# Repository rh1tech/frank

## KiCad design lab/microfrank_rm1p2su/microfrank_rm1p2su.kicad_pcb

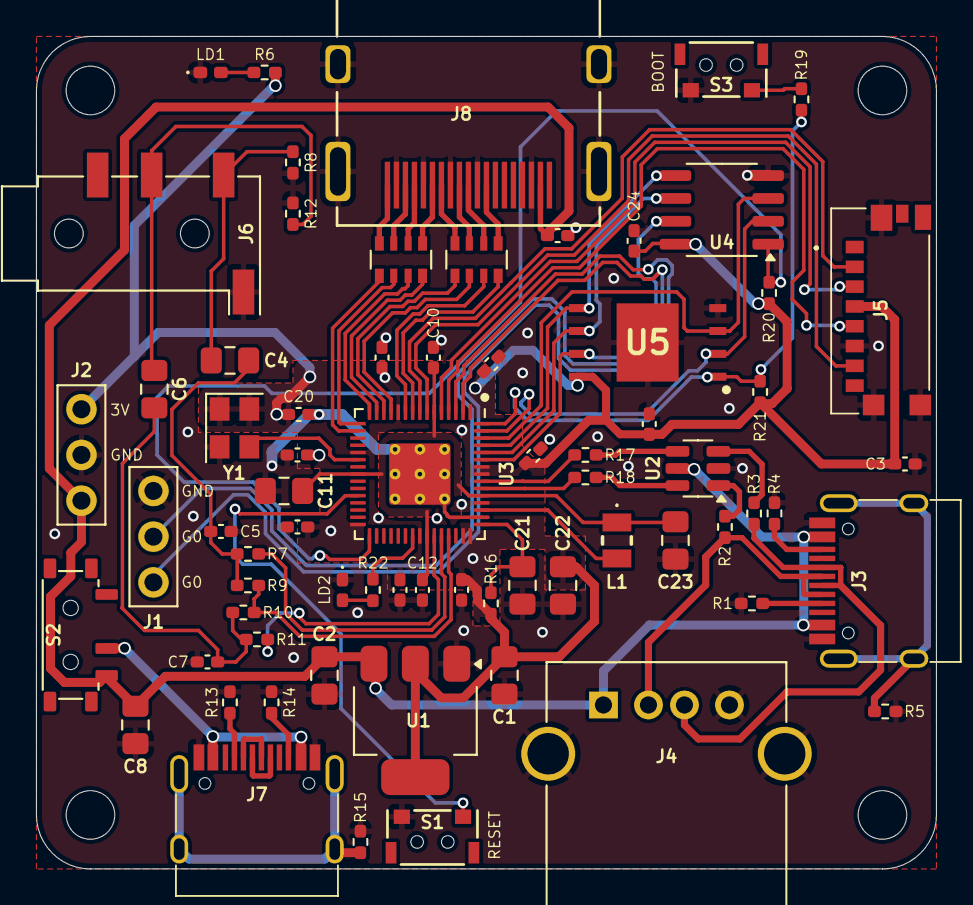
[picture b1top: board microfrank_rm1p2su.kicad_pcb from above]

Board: 2 copper layers, 50.0 x 46.2 mm, 73 parts (0 on the bottom side), 65 nets.

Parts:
C1, C2, C4, C6, C8: 10u; Capacitor (0805)
C3, C9, C10, C12, C13, C14, C15, C16, C17, C18, C19, C20, C24, C25: 100n; Capacitor (0402)
C5, C7: 10n; Capacitor (0402)
C11, C21, C22, C23: 4.7u; Capacitor (0805)
H1, H2, H3, H4: MountingHole; Mounting Hole (2.7mm)
J1: UART; Pin Header (1x03)
J2: PWR; Pin Header (1x03)
J3, J7: USB4215-03-A; USB Type C
J4: 676430910; USB Type A (single)
J5: 0475710001; MicroSD (SMD, short)
J6: PJ-320D; Jack (3.5mm, PJ-320D)
J8: DC3RX19JA2; HDMI (female)
L1: 3.3u; Inductor (0806)
LD1: Power; LED (0402)
LD2: Blue; LED (0402)
R1, R4, R13, R14: 5.1K; Resistor (0402)
R2, R3: 22R; Resistor (0402)
R5, R15: 1M; Resistor (0402)
R6, R7, R11, R19, R22: 1K; Resistor (0402)
R8, R12: 330R; Resistor (0402)
R9, R10: 2K; Resistor (0402)
R16: 33R; Resistor (0402)
R17, R18: 27R; Resistor (0402)
R20, R21: 10K; Resistor (0402)
RN1, RN2: 270R; Resistor Array (4x0603)
S1: Reset; TACT-SIDE-4623
S2: MSK12C02; Switch (MSK12C02)
S3: TS-1233; TACT-SIDE-4623
U1: NCP1117 3.3; SOT-223
U2: USBLC6-2SC6; SOT-23-6
U3: RP2350; QFN 60 (RP2350A)
U4: ESP-PSRAM32; SO-8
U5: W25Q128JVS; SON127P800X600X80-9N-D
Y1: ASE-12MHz; Crystal (3225, active)

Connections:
+1V1: C10.1, C11.1, C12.1, C23.1, L1.1, U3.6 (DVDD), U3.23 (DVDD), U3.39 (DVDD), U3.50 (VREG_FB)
+3V3: C1.1, C3.2, C13.1, C14.1, C15.1, C16.1, C17.1, C18.1, C19.1, C20.1, C22.1, C24.1, C25.1, J2.1, J5.P4 (VDD), R6.2, R16.1, R20.2, R21.1, U1.2 (VO), U3.1 (IOVDD), U3.11 (IOVDD), U3.20 (IOVDD), U3.30 (IOVDD), U3.38 (IOVDD), U3.44 (ADC_AVDD), U3.45 (IOVDD), U3.49 (VREG_VIN), U3.53 (USB_OTP_VDD), U3.54 (QSPI_IOVDD), U4.8 (VCC), U5.8 (VCC), Y1.1 (EN), Y1.4 (Vdd)
/Audio Out/L: C4.1, J6.T, R8.1
/Audio Out/R: C6.1, J6.R, R12.1
/GPIO0: J1.2, U3.2 (GPIO0)
/GPIO1: J1.3, U3.3 (GPIO1)
/GPIO2: J5.P5 (CLK), U3.4 (GPIO2)
/GPIO3: J5.P3 (CMD), U3.5 (GPIO3)
/GPIO4: J5.P7 (DAT0), U3.7 (GPIO4)
/GPIO5: J5.P2 (CD/DAT3), U3.8 (GPIO5)
/GPIO6: RN1.4 (R4.1), U3.9 (GPIO6)
/GPIO7: RN1.3 (R3.1), U3.10 (GPIO7)
/GPIO8: RN1.2 (R2.1), U3.12 (GPIO8)
/GPIO9: RN1.1 (R1.1), U3.13 (GPIO9)
/GPIO10: RN2.4 (R4.1), U3.14 (GPIO10)
/GPIO11: RN2.3 (R3.1), U3.15 (GPIO11)
/GPIO12: RN2.2 (R2.1), U3.16 (GPIO12)
/GPIO13: RN2.1 (R1.1), U3.17 (GPIO13)
/GPIO19: R20.1, U3.31 (GPIO19), U4.1 (~CE)
/GPIO26: R11.2, U3.40 (GPIO26_ADC0)
/GPIO27: R7.2, U3.41 (GPIO27_ADC1)
/GPIO28: R9.2, R10.2, U3.42 (GPIO28_ADC2)
/PW_D+: R17.1, U2.4 (I/O2)
/PW_D-: R18.1, U2.6 (I/O1)
/RP2350A/QSPI_SCLK: U3.56 (QSPI_SCLK), U4.6 (SCLK), U5.6 (CLK)
/RP2350A/QSPI_SD0: U3.57 (QSPI_SD0), U4.5 (SI/SIO), U5.5 (DI(IO0))
/RP2350A/QSPI_SD1: U3.59 (QSPI_SD1), U4.2 (SO/SIO), U5.2 (DO(IO1))
/RP2350A/QSPI_SD2: U3.58 (QSPI_SD2), U4.3 (SIO2), U5.3 (IO2)
/RP2350A/QSPI_SD3: U3.55 (QSPI_SD3), U4.7 (SIO3), U5.7 (IO3)
/RP2350A/QSPI_SS: R19.1, R21.2, U3.60 (QSPI_SS), U5.1 (~CS)
/RP2350A/VREG_AVDD: C21.1, R16.2, U3.46 (VREG_AVDD)
/RP2350A/VREG_LX: L1.2, U3.48 (VREG_LX)
/RP2350A/XIN: U3.21 (XIN), Y1.3 (OUT)
/RP2350A/~USB_BOOT: R19.2, S3.2
/RUN: S1.1, U3.26 (RUN)
GND: C1.2, C2.2, C3.1, C5.2, C7.2, C8.2, C9.2, C10.2, C11.2, C12.2, C13.2, C14.2, C15.2, C16.2, C17.2, C18.2, C19.2, C20.2, C21.2, C22.2, C23.2, C24.2, C25.2, J1.1, J2.2, J3.1 (GND), J3.12 (GND), J4.4 (GND), J4.5 (Shield), J5.G1 (GND_1), J5.G2 (GND_2), J5.G3 (GND_3), J5.P6 (VSS), J6.S, J7.1 (GND), J7.12 (GND), J8.2 (G_D2), J8.5 (G_D1), J8.8 (G_D0), J8.11 (G_CLK), J8.17 (G_DDC/CEC), J8.20 (SHIELD1), J8.21 (SHIELD2), J8.22 (SHIELD3), J8.23 (SHIELD4), LD1.1 (K), LD2.1 (K), R1.1, R4.1, R5.2, R8.2, R12.2, R13.1, R14.1, R15.2, S1.2, S3.1, U1.1 (GND), U2.2 (GND), U3.47 (VREG_PGND), U3.61 (GND), U4.4 (VSS), U5.4 (GND), Y1.2 (GND)
GPIO25: R22.2, U3.37 (GPIO25)
unnamed: C4.2, C5.1, R7.1, R9.1
unnamed: C6.2, C7.1, R10.1, R11.1
unnamed: J3.4 (CC1), R1.2
unnamed: J3.10 (CC2), R4.2
unnamed: J3.5 (DN2), J3.7 (DN1), J4.2 (D-), R2.2
unnamed: J3.6 (DP1), J3.8 (DP2), J4.3 (D+), R3.2
unnamed: J3.13 (SHIELD), R5.1
unnamed: J7.4 (CC1), R13.2
unnamed: J7.10 (CC2), R14.2
unnamed: J7.5 (DN2), J7.7 (DN1)
unnamed: J7.6 (DP1), J7.8 (DP2)
unnamed: J7.13 (SHIELD), R15.1
unnamed: J8.12 (CLKN), RN1.5 (R4.2)
unnamed: J8.10 (CLKP), RN1.6 (R3.2)
unnamed: J8.9 (D0N), RN1.7 (R2.2)
unnamed: J8.7 (D0P), RN1.8 (R1.2)
unnamed: J8.6 (D1N), RN2.5 (R4.2)
unnamed: J8.4 (D1P), RN2.6 (R3.2)
unnamed: J8.3 (D2N), RN2.7 (R2.2)
unnamed: J8.1 (D2P), RN2.8 (R1.2)
unnamed: LD1.2 (A), R6.1
unnamed: LD2.2 (A), R22.1
unnamed: R2.1, U2.1 (I/O1)
unnamed: R3.1, U2.3 (I/O2)
unnamed: J7.2 (VBUS), J7.11 (VBUS), S2.2 (B)
unnamed: R18.2, U3.51 (USB_DM)
unnamed: R17.2, U3.52 (USB_DP)
VBUS: C2.1, C8.1, C9.1, J2.3, J3.2 (VBUS), J3.11 (VBUS), J4.1 (VBUS), J8.18 (+5V), S2.3 (A), U1.3 (VI), U2.5 (VBUS)

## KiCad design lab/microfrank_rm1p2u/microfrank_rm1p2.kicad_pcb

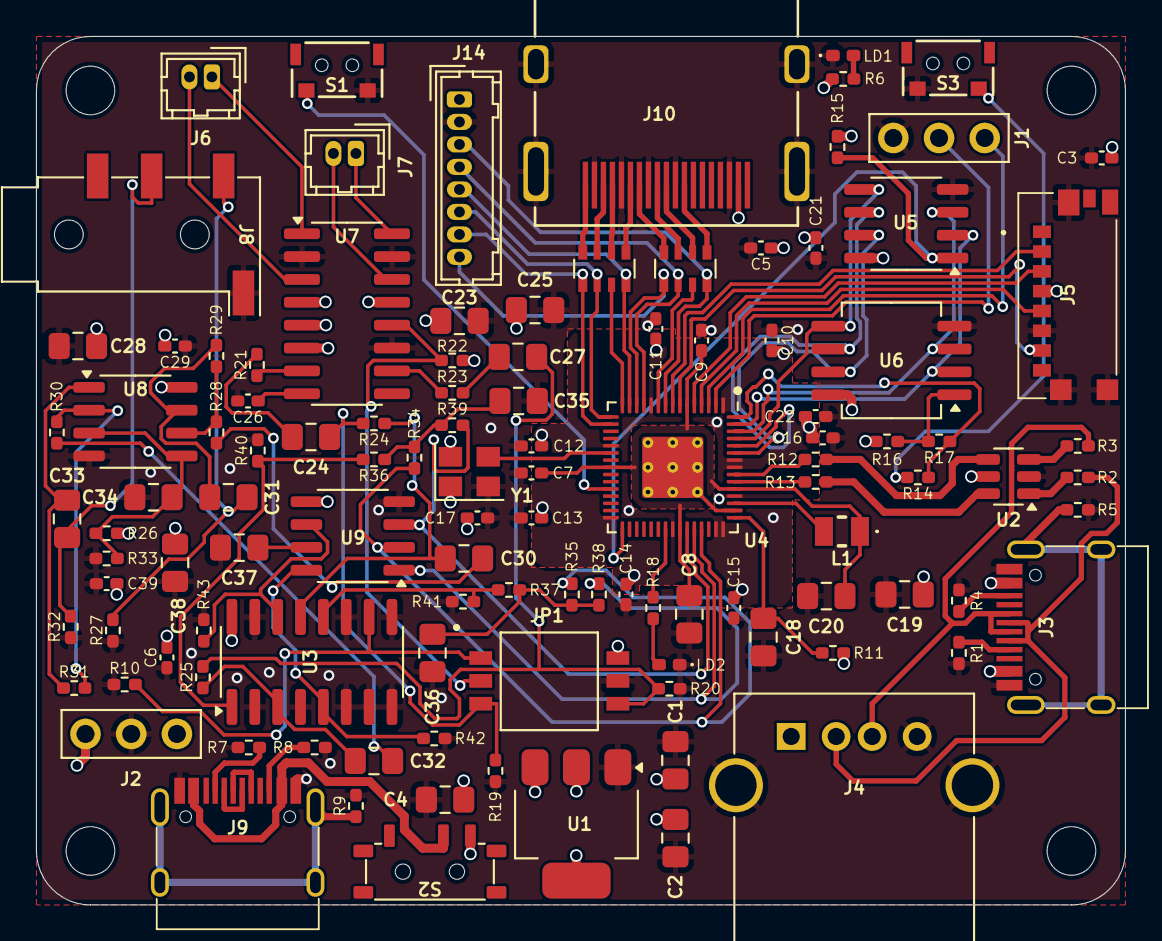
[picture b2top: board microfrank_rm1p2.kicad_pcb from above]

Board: 4 copper layers, 60.5 x 48.2 mm, 116 parts (0 on the bottom side), 93 nets.

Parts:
C1, C2, C4, C28, C30, C31, C32, C33, C34, C37, C38: 10u; Capacitor (0805)
C3, C5, C6, C7, C9, C10, C11, C12, C13, C14, C15, C16, C17, C21, C22, C26, C29, C39: 100n; Capacitor (0402)
C8, C18, C19, C20: 4.7u; Capacitor (0805)
C23, C24, C27: 1u; Capacitor (0805)
C25: 47u; Capacitor (0805)
C35, C36: 47n; Capacitor (0805)
H1, H2, H3, H4: MountingHole; Mounting Hole (2.7mm)
J1: UART; Pin Header (1x03)
J2: PWR; Pin Header (1x03)
J3, J9: USB4215-03-A; USB Type C
J4: 676430910; USB Type A (single)
J5: 0475710001; MicroSD (SMD, short)
J6: PAM L; Connector Female 1.25 JST 2P
J7: PAM R; Connector Female 1.25 JST 2P
J8: PJ-320D; Jack (3.5mm, PJ-320D)
J10: DC3RX19JA2; HDMI (female)
J14: Pin Header 1x08; Connector Female 1.25 JST 8P
JP1: Main Jumpers; Jumper (SMD, 3 Pin)
L1: 3.3u; Inductor (0806)
LD1: Power; LED (0402)
LD2: Blue; LED (0402)
R1, R4, R7, R8: 5.1K; Resistor (0402)
R2, R3: 22R; Resistor (0402)
R5, R9: 1M; Resistor (0402)
R6, R14, R18, R38, R39: 1K; Resistor (0402)
R10, R15, R16, R21, R22, R23, R24, R25, R26, R28, R30, R33, R36, R37: 10K; Resistor (0402)
R11: 33R; Resistor (0402)
R12, R13: 27R; Resistor (0402)
R17: 0R; Resistor (0402)
R19, R20, R34, R35, R40, R41: 2K; Resistor (0402)
R27, R32: 20K; Resistor (0402)
R29, R31: 47K; Resistor (0402)
R42, R43: 470R; Resistor (0402)
RN1, RN2: 270R; Resistor Array (4x0603)
S1: Reset; TACT-SIDE-4623
S2: MSK12C02; Switch (MSK12C02)
S3: TS-1233; TACT-SIDE-4623
U1: NCP1117 3.3; SOT-223
U2: USBLC6-2SC6; SOT-23-6
U3: 74HC4052D; SOP-16
U4: RP2350; QFN 60 (RP2350A)
U5: ESP-PSRAM32; SO-8
U6: W25Q128JVS; SOIC-8
U7: PAM8403D; SOP-16
U8: LM358; SO-8
U9: TDA1387T; SO-8
Y1: ASE-12MHz; Crystal (3225, active)

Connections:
+1V1: C7.1, C8.1, C9.1, C20.1, L1.1, U4.6 (DVDD), U4.23 (DVDD), U4.39 (DVDD), U4.50 (VREG_FB)
+3V3: C1.1, C3.2, C6.2, C10.1, C11.1, C12.1, C13.1, C14.1, C15.1, C16.1, C17.1, C19.1, C21.1, C22.1, J2.1, J5.P4 (VDD), JP1.6, R6.2, R11.1, R15.2, R16.1, U1.2 (VO), U3.16 (VCC), U4.1 (IOVDD), U4.11 (IOVDD), U4.20 (IOVDD), U4.30 (IOVDD), U4.38 (IOVDD), U4.44 (ADC_AVDD), U4.45 (IOVDD), U4.49 (VREG_VIN), U4.53 (USB_OTP_VDD), U4.54 (QSPI_IOVDD), U5.8 (VCC), U6.8 (VCC), Y1.1 (EN), Y1.4 (Vdd)
/AMP_IN_L: C30.1, R24.1, U3.13 (1Z)
/AMP_IN_R: C32.1, R25.1, U3.3 (2Z)
/AUDIOSW: JP1.1, R10.2, U3.10 (S0)
/Audio Out/AMP_OUTL: C31.2, J8.T, R27.2
/Audio Out/AMP_OUTR: C33.2, J8.R, R32.2
/Audio Out/AMP_PAM_OUTL_M: J6.2, U7.3 (-OUTL)
/Audio Out/AMP_PAM_OUTL_P: J6.1, U7.1 (+OUT_L)
/Audio Out/AMP_PAM_OUTR_M: J7.2, U7.14 (-OUT_R)
/Audio Out/AMP_PAM_OUTR_P: J7.1, U7.16 (+OUT_R)
/GPIO0: J1.2, U4.2 (GPIO0)
/GPIO1: J1.3, U4.3 (GPIO1)
/GPIO2: J5.P5 (CLK), U4.4 (GPIO2)
/GPIO3: J5.P3 (CMD), U4.5 (GPIO3)
/GPIO4: J5.P7 (DAT0), U4.7 (GPIO4)
/GPIO5: J5.P2 (CD/DAT3), U4.8 (GPIO5)
/GPIO6: J14.3, RN1.4 (R4.1), U4.9 (GPIO6)
/GPIO7: RN1.3 (R3.1), U4.10 (GPIO7)
/GPIO8: J14.4, RN1.2 (R2.1), U4.12 (GPIO8)
/GPIO9: J14.8, RN1.1 (R1.1), U4.13 (GPIO9)
/GPIO10: J14.5, RN2.4 (R4.1), U4.14 (GPIO10)
/GPIO11: RN2.3 (R3.1), U4.15 (GPIO11)
/GPIO12: J14.6, RN2.2 (R2.1), U4.16 (GPIO12)
/GPIO13: J14.7, RN2.1 (R1.1), U4.17 (GPIO13)
/GPIO19: R15.1, U4.31 (GPIO19), U5.1 (~CE)
/GPIO26: R39.2, U4.40 (GPIO26_ADC0), U9.3 (DATA)
/GPIO27: R38.2, U4.41 (GPIO27_ADC1), U9.1 (SCLK)
/GPIO28: R34.1, R35.1, U4.42 (GPIO28_ADC2), U9.2 (LRCK)
/MONO_L: C24.1, JP1.3, R19.1, R24.2
/MONO_R: C27.1, JP1.4, R20.1, R25.2
/PWM_OUT_L: R37.2, R41.1, U3.12 (1Y0)
/PWM_OUT_R: R36.2, R40.1, U3.1 (2Y0)
/PW_D+: R12.1, U2.4 (I/O2)
/PW_D-: R13.1, U2.6 (I/O1)
/RP2350A/FLASH_SS: R16.2, R17.2, U6.1 (~CS)
/RP2350A/QSPI_SCLK: U4.56 (QSPI_SCLK), U5.6 (SCLK), U6.6 (CLK)
/RP2350A/QSPI_SD0: U4.57 (QSPI_SD0), U5.5 (SI/SIO), U6.5 (DI(IO0))
/RP2350A/QSPI_SD1: U4.59 (QSPI_SD1), U5.2 (SO/SIO), U6.2 (DO(IO1))
/RP2350A/QSPI_SD2: U4.58 (QSPI_SD2), U5.3 (SIO2), U6.3 (IO2)
/RP2350A/QSPI_SD3: U4.55 (QSPI_SD3), U5.7 (SIO3), U6.7 (IO3)
/RP2350A/QSPI_SS: R14.1, R17.1, U4.60 (QSPI_SS)
/RP2350A/VREG_AVDD: C18.1, R11.2, U4.46 (VREG_AVDD)
/RP2350A/VREG_LX: L1.2, U4.48 (VREG_LX)
/RP2350A/XIN: U4.21 (XIN), Y1.3 (OUT)
/RP2350A/~USB_BOOT: R14.2, S3.2
/RUN: S1.1, U4.26 (RUN)
/SHND: JP1.2, R22.2, U7.12 (SHND)
/TDA_L: R43.2, U3.14 (1Y1), U9.6 (A_LEFT)
/TDA_R: R42.1, U3.5 (2Y1), U9.8 (A_RIGHT)
GND: C1.2, C2.2, C3.1, C4.2, C5.2, C6.1, C7.2, C8.2, C9.2, C10.2, C11.2, C12.2, C13.2, C14.2, C15.2, C16.2, C17.2, C18.2, C19.2, C20.2, C21.2, C22.2, C23.2, C25.2, C26.2, C28.1, C29.1, C34.1, C35.2, C36.2, C37.2, C38.2, C39.2, J1.1, J2.2, J3.1 (GND), J3.12 (GND), J4.4 (GND), J4.5 (Shield), J5.G1 (GND_1), J5.G2 (GND_2), J5.G3 (GND_3), J5.P6 (VSS), J8.S, J9.1 (GND), J9.12 (GND), J10.2 (G_D2), J10.5 (G_D1), J10.8 (G_D0), J10.11 (G_CLK), J10.17 (G_DDC/CEC), J10.20 (SHIELD1), J10.21 (SHIELD2), J10.22 (SHIELD3), J10.23 (SHIELD4), J14.2, JP1.5, LD1.1 (K), LD2.1 (K), R1.1, R4.1, R5.2, R7.1, R8.1, R9.2, R10.1, R19.2, R20.2, R27.1, R32.1, R33.1, R40.2, R41.2, R42.2, R43.1, S1.2, S3.1, U1.1 (GND), U2.2 (GND), U3.2 (2Y2), U3.4 (2Y3), U3.6 (~E), U3.7 (VEE), U3.8 (GND), U3.9 (S1), U3.11 (1Y3), U3.15 (1Y2), U4.47 (VREG_PGND), U4.61 (GND), U5.4 (VSS), U6.4 (GND), U7.2 (PGND), U7.11 (GND), U7.15 (PGND), U8.4 (V-), U9.4 (AGND), Y1.2 (GND)
GPIO25: R18.2, U4.37 (GPIO25)
unnamed: C24.2, R21.2
unnamed: C27.2, R23.2
unnamed: C30.2, R28.2
unnamed: C31.1, R29.1, U8.7
unnamed: C32.2, R30.2
unnamed: C33.1, R31.1, U8.1
unnamed: C35.1, R34.2, R36.1, R39.1
unnamed: C36.1, R35.2, R37.1, R38.1
unnamed: J3.4 (CC1), R1.2
unnamed: J3.10 (CC2), R4.2
unnamed: J3.5 (DN2), J3.7 (DN1), J4.2 (D-), R2.2
unnamed: J3.6 (DP1), J3.8 (DP2), J4.3 (D+), R3.2
unnamed: J3.13 (SHIELD), R5.1
unnamed: J9.4 (CC1), R7.2
unnamed: J9.10 (CC2), R8.2
unnamed: J9.5 (DN2), J9.7 (DN1)
unnamed: J9.6 (DP1), J9.8 (DP2)
unnamed: J9.13 (SHIELD), R9.1
unnamed: J10.12 (CLKN), RN1.5 (R4.2)
unnamed: J10.10 (CLKP), RN1.6 (R3.2)
unnamed: J10.9 (D0N), RN1.7 (R2.2)
unnamed: J10.7 (D0P), RN1.8 (R1.2)
unnamed: J10.6 (D1N), RN2.5 (R4.2)
unnamed: J10.4 (D1P), RN2.6 (R3.2)
unnamed: J10.3 (D2N), RN2.7 (R2.2)
unnamed: J10.1 (D2P), RN2.8 (R1.2)
unnamed: LD1.2 (A), R6.1
unnamed: LD2.2 (A), R18.1
unnamed: R2.1, U2.1 (I/O1)
unnamed: R3.1, U2.3 (I/O2)
unnamed: J9.2 (VBUS), J9.11 (VBUS), S2.2 (B)
unnamed: R13.2, U4.51 (USB_DM)
unnamed: R12.2, U4.52 (USB_DP)
unnamed: R21.1, U7.7 (INL)
unnamed: R23.1, U7.10 (INR)
unnamed: C26.1, U7.8 (VREF)
unnamed: C34.2, R26.1, R33.2, U8.3 (+), U8.5 (+)
unnamed: R30.1, R31.2, U8.2 (-)
unnamed: R28.1, R29.2, U8.6 (-)
unnamed: C37.1, U9.7 (FLT)
VBUS: C2.1, C4.1, C5.1, C23.1, C25.1, C28.2, C29.2, C38.1, C39.1, J2.3, J3.2 (VBUS), J3.11 (VBUS), J4.1 (VBUS), J10.18 (+5V), J14.1, R22.1, R26.2, S2.3 (A), U1.3 (VI), U2.5 (VBUS), U7.4 (PVDD), U7.5 (MUTE), U7.6 (VDD), U7.13 (PVDD), U8.8 (V+), U9.5 (VA)

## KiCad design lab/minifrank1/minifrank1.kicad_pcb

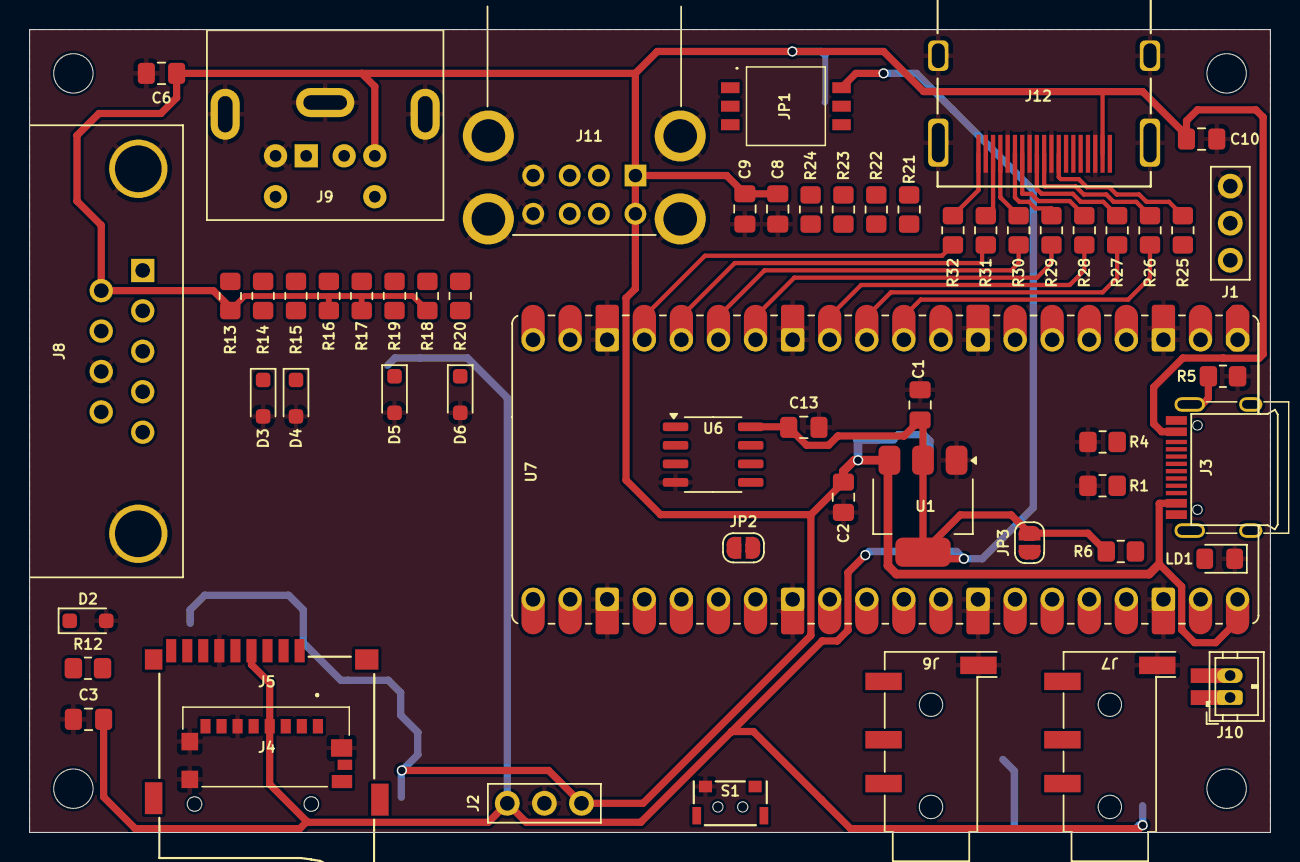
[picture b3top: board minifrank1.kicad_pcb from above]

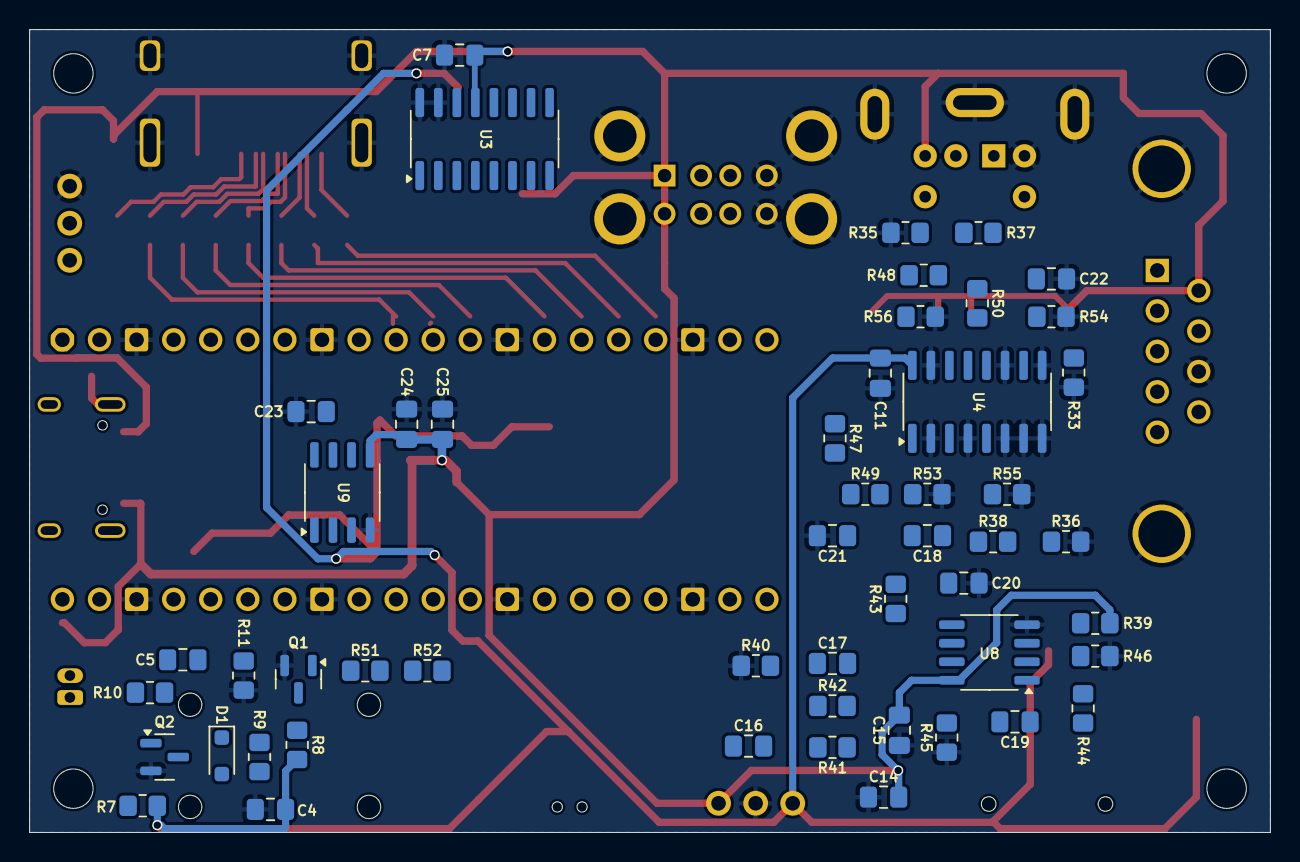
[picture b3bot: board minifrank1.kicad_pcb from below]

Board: 2 copper layers, 85.0 x 55.0 mm, 113 parts (51 on the bottom side), 91 nets.

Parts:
C1, C2, C8, C9, C14, C16, C17, C18, C19, C20, C23, C24: 10u; Capacitor (0805)
C3, C4, C5, C6, C10, C11, C13, C15, C25: 100n; Capacitor (0805)
C7: 4.7u; Capacitor (0805)
C21, C22: 47n; Capacitor (0805)
D1: 1N4148; Diode (SOD-323)
D2, D3, D4, D5, D6: 3V3; Diode (SOD-323)
H1, H2, H3, H4: MountingHole; Mounting Hole (2.7mm)
J1: UART; Pin Header (1x03)
J2: PWR; Pin Header (1x03)
J3: USB4215-03-A; USB Type C
J4: 0475710001; MicroSD (SMD, short)
J5: 104031-0811; MicroSD (SMD, long)
J6, J7: PJ-320D; Jack (3.5mm, PJ-320D)
J8: D-SUB 9 Male; D-SUB (9 pin, male, top mount)
J9: MDC-036; MiniDIN (6 Pin, female)
J10: USB HUB Data; Connector Female ZH 1.50mm (2 pins + tracks)
J11: SS-52100-004; USB Type A (stacked)
J12: DC3RX19JA2; HDMI (female)
JP1: Main Jumpers; DS05127203BKSMTTR
JP2, JP3: Jumper (Solder); Jumper (solder)
LD1: Power; LED (0805)
Q1, Q2: BC850; SOT-23
R1, R4: 5.1K; Resistor (0805)
R5: 1M; Resistor (0805)
R6, R8, R12, R13, R16, R17, R18, R51, R52: 1K; Resistor (0805)
R7, R9, R10, R33, R37, R38, R39, R41, R43, R46, R49, R50: 10K; Resistor (0805)
R11, R14, R15, R19, R20: 100R; Resistor (0805)
R21, R22, R23, R24: 22R; Resistor (0805)
R25, R26, R27, R28, R29, R30, R31, R32: 270R; Resistor (0805)
R35, R36, R47, R48, R53, R54: 2K; Resistor (0805)
R40, R45: 20K; Resistor (0805)
R42, R44: 47K; Resistor (0805)
R55, R56: 470R; Resistor (0805)
S1: Reset; TACT-SIDE-4623
U1: NCP1117 3.3; SOT-223
U3: MW7211A; SOP-16
U4: 74HC4052D; SOP-16
U6: ESP-PSRAM32; SO-8
U7: Rasberry Pi Pico; Raspberry Pi Pico
U8: LM358; SO-8
U9: TDA1387T; SO-8

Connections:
+3V3: C1.1, C3.2, C4.1, C11.2, C13.1, J2.1, J4.P4 (VDD), J5.4 (VDD), JP1.6, JP3.2 (B), R6.2, R7.1, R8.1, U1.2 (VO), U4.16 (VCC), U6.8 (VCC)
/AMP_IN_L: C16.1, R37.1, U4.13 (1Z)
/AMP_IN_R: C18.1, R38.1, U4.3 (2Z)
/AUDIOSW: JP1.1, R33.2, U4.10 (S0)
/Audio Out/AMP_OUTL: C17.2, J6.T, R40.2
/Audio Out/AMP_OUTR: C19.2, J6.R, R45.2
/GPIO0: D3.1 (K), J1.2, R14.2, U7.1 (GPIO0)
/GPIO1: D4.1 (K), J1.3, R15.2, U7.2 (GPIO1)
/GPIO2: J4.P5 (CLK), J5.5 (CLK), U7.4 (GPIO2)
/GPIO3: J4.P3 (CMD), J5.3 (CMD), U7.5 (GPIO3)
/GPIO4: J4.P7 (DAT0), J5.7 (DAT0), U7.6 (GPIO4)
/GPIO5: J4.P2 (CD/DAT3), J5.2 (DAT3/CD), U7.7 (GPIO5)
/GPIO6: R25.2, U7.9 (GPIO6)
/GPIO7: R26.2, U7.10 (GPIO7)
/GPIO8: R27.2, U7.11 (GPIO8)
/GPIO9: R28.2, U7.12 (GPIO9)
/GPIO10: R29.2, U7.14 (GPIO10)
/GPIO11: R30.2, U7.15 (GPIO11)
/GPIO12: R31.2, U7.16 (GPIO12)
/GPIO13: R32.2, U7.17 (GPIO13)
/GPIO14: J8.4, JP1.5, U7.19 (GPIO14)
/GPIO15: J8.3, JP1.4, U7.20 (GPIO15)
/GPIO16: D2.1 (K), R12.1, U7.21 (GPIO16)
/GPIO18: U6.1 (~CE), U7.24 (GPIO18)
/GPIO19: U6.6 (SCLK), U7.25 (GPIO19)
/GPIO20: U6.5 (SI/SIO), U7.26 (GPIO20)
/GPIO21: JP2.2 (B), U7.27 (GPIO21)
/GPIO22: Q1.3 (C), R8.2, U7.29 (GPIO22)
/GPIO26: R52.2, U7.31 (GPIO26_ADC0), U9.3 (DATA)
/GPIO27: R51.2, U7.32 (GPIO27_ADC1), U9.1 (SCLK)
/GPIO28: R47.1, R48.1, U7.34 (GPIO28_ADC2), U9.2 (LRCK)
/KB_CLK: J9.5, R13.2, R14.1
/KB_DATA: J9.1, R15.1, R16.2
/MS_CLK: J9.6, R18.2, R20.1
/MS_CLK_3V: D6.1 (K), JP1.2, R20.2
/MS_DATA: J9.2, R17.2, R19.1
/MS_DATA_3V: D5.1 (K), JP1.3, R19.2
/PWM_OUT_L: R50.2, R54.1, U4.12 (1Y0)
/PWM_OUT_R: R49.2, R53.1, U4.1 (2Y0)
/Power/D+: J3.6 (DP1), J3.8 (DP2)
/Power/D-: J3.5 (DN2), J3.7 (DN1)
/RUN: S1.1, U7.30 (RUN)
/SD Card/DAT1: J4.P8 (DAT1), J5.8 (DAT1)
/SD Card/DAT2: J4.P1 (DAT2), J5.1 (DAT2)
/TDA_L: R56.2, U4.14 (1Y1), U9.6 (A_LEFT)
/TDA_R: R55.1, U4.5 (2Y1), U9.8 (A_RIGHT)
/USB Hub/DM_IN: J10.2, U3.10 (DMU)
/USB Hub/DP_IN: J10.1, U3.11 (DPU)
/USB_D1+: R21.1, U3.8 (DP3)
/USB_D1-: R23.1, U3.7 (DM3)
/USB_D2+: R22.1, U3.6 (DP2)
/USB_D2-: R24.1, U3.5 (DM2)
GND: C1.2, C2.2, C3.1, C4.2, C6.2, C7.2, C8.2, C9.2, C10.2, C11.1, C13.2, C14.1, C15.1, C20.1, C21.2, C22.2, C23.2, C24.2, C25.2, D2.2 (A), D3.2 (A), D4.2 (A), D5.2 (A), D6.2 (A), J1.1, J2.2, J3.1 (GND), J3.12 (GND), J4.G1 (GND_1), J4.G2 (GND_2), J4.G3 (GND_3), J4.P6 (VSS), J5.6 (VSS), J6.S, J7.S, J8.8, J9.3, J11.4 (GND1), J11.8 (GND2), J11.9 (Shield), J12.2 (G_D2), J12.5 (G_D1), J12.8 (G_D0), J12.11 (G_CLK), J12.17 (G_DDC/CEC), J12.20 (SHIELD1), J12.21 (SHIELD2), J12.22 (SHIELD3), J12.23 (SHIELD4), LD1.1 (K), Q1.2 (E), Q2.2 (E), R1.1, R4.1, R5.2, R11.2, R33.1, R35.2, R36.2, R40.1, R45.1, R46.1, R53.2, R54.2, R55.2, R56.1, S1.2, U1.1 (GND), U3.15 (GND), U3.16 (GND), U4.2 (2Y2), U4.4 (2Y3), U4.6 (~E), U4.7 (VEE), U4.8 (GND), U4.9 (S1), U4.11 (1Y3), U4.15 (1Y2), U6.4 (VSS), U7.3 (GND), U7.8 (GND), U7.13 (GND), U7.18 (GND), U7.23 (GND), U7.28 (GND), U7.33 (AGND), U7.38 (GND), U8.4 (V-), U9.4 (AGND)
unnamed: C5.1, J7.T, R11.1
unnamed: C5.2, R10.1
unnamed: C16.2, R41.2
unnamed: C17.1, R42.1, U8.7
unnamed: C18.2, R43.2
unnamed: C19.1, R44.1, U8.1
unnamed: C21.1, R47.2, R49.1, R52.1
unnamed: C22.1, R48.2, R50.1, R51.1
unnamed: D1.2 (A), Q2.3 (C), R7.2, R9.1
unnamed: D1.1 (K), Q2.1 (B), R10.2
unnamed: J3.4 (CC1), R1.2
unnamed: J3.10 (CC2), R4.2
unnamed: J3.13 (SHIELD), R5.1
unnamed: J8.2, R12.2
unnamed: J11.3 (D1+), R21.2
unnamed: J11.2 (D1-), R23.2
unnamed: J11.7 (D2+), R22.2
unnamed: J11.6 (D2-), R24.2
unnamed: J12.12 (CLKN), R25.1
unnamed: J12.10 (CLKP), R26.1
unnamed: J12.9 (D0N), R27.1
unnamed: J12.7 (D0P), R28.1
unnamed: J12.6 (D1N), R29.1
unnamed: J12.4 (D1P), R30.1
unnamed: J12.3 (D2N), R31.1
unnamed: J12.1 (D2P), R32.1
unnamed: JP2.1 (A), U6.2 (SO/SIO)
unnamed: JP3.1 (A), U7.36 (3V3)
unnamed: LD1.2 (A), R6.1
unnamed: Q1.1 (B), R9.2
unnamed: R35.1, R37.2
unnamed: R36.1, R38.2
unnamed: U3.12 (VD33), U3.14 (VD3)
unnamed: C20.2, R39.1, R46.2, U8.3 (+), U8.5 (+)
unnamed: R43.1, R44.2, U8.2 (-)
unnamed: R41.1, R42.2, U8.6 (-)
unnamed: C23.1, U9.7 (FLT)
VBUS: C2.1, C6.1, C7.1, C8.1, C9.1, C10.1, C14.2, C15.2, C24.1, C25.1, J2.3, J3.2 (VBUS), J3.11 (VBUS), J8.6, J9.4, J11.1 (VBUS1), J11.5 (VBUS2), J12.18 (+5V), R13.1, R16.1, R17.1, R18.1, R39.2, U1.3 (VI), U3.13 (VDD5), U7.40 (VBUS), U8.8 (V+), U9.5 (VA)

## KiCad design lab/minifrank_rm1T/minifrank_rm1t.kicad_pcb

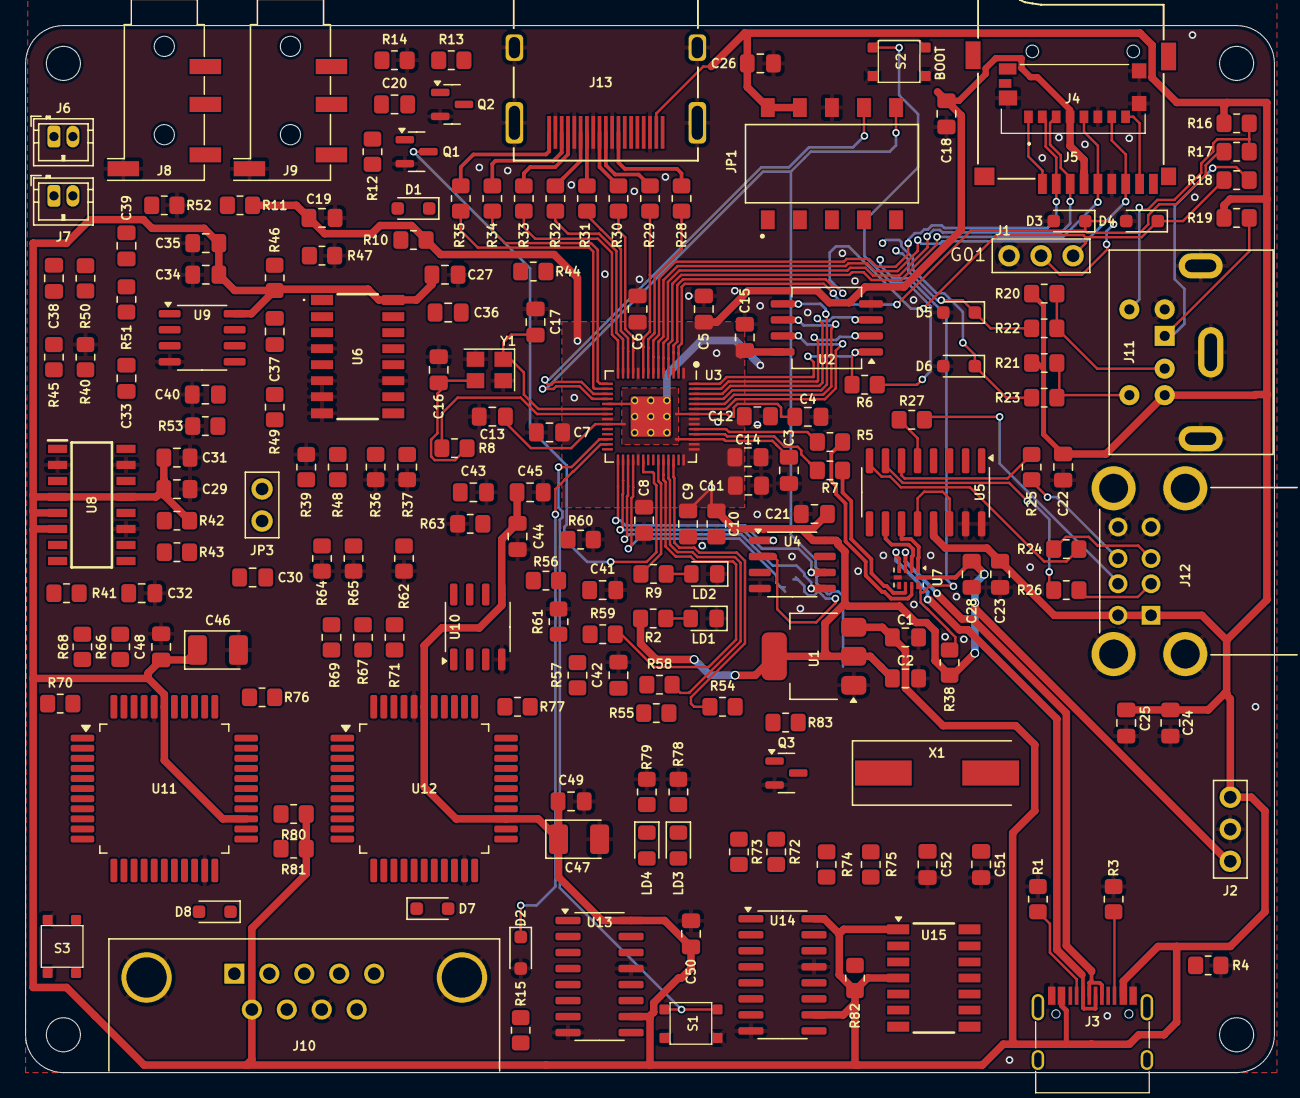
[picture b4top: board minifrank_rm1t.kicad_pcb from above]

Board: 2 copper layers, 99.0 x 83.0 mm, 190 parts (1 on the bottom side), 152 nets.

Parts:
C1, C2, C24, C25, C34, C36, C37, C38, C39, C40, C43, C44: 10u; Capacitor (0805)
C3, C4, C5, C6, C7, C8, C9, C10, C11, C12, C15, C18, C19, C20, C21, C22, C26, C27, C28, C32, C35, C45, C48, C49, C50: 100n; Capacitor (0805)
C13, C14, C29, C30, C33: 1u; Capacitor (0805)
C16, C17: 15p; Capacitor (0805)
C23: 4.7u; Capacitor (0805)
C31: 47u; Capacitor (0805)
C41, C42: 47n; Capacitor (0805)
C46, C47: 100u; Capacitor (3528, tantalum, polar)
C51, C52: 22p; Capacitor (0805)
D1, D7, D8: 1N4148; Diode (SOD-323)
D2, D3, D4, D5, D6: 3V3; Diode (SOD-323)
H1, H2, H3, H4: MountingHole; Mounting Hole (2.7mm)
J1: UART; Pin Header (1x03)
J2: PWR; Pin Header (1x03)
J3: USB4215-03-A; USB Type C
J4: 0475710001; MicroSD (SMD, short)
J5: 104031-0811; MicroSD (SMD, long)
J6: PAM L; Connector Female ZH 1.50mm (2 pins)
J7: PAM R; Connector Female ZH 1.50mm (2 pins)
J8, J9: PJ-320D; Jack (3.5mm, PJ-320D)
J10: D-SUB 9 Male; D-SUB (9 pin, male, top mount)
J11: MDC-036; MiniDIN (6 Pin, female)
J12: SS-52100-004; USB Type A (stacked)
J13: DC3RX19JA2; HDMI (female)
JP1: Main Jumpers; SW_DS04-254-2-05BK-SMT-TR
JP2: Jumper (Solder); Jumper (solder)
JP3: Mono; Pin Header (1x02)
LD1: Green; LED (0805)
LD2: Blue; LED (0805)
LD3, LD4: Orange; LED (0805)
Q1, Q2, Q3: BC850; SOT-23
R1, R3: 5.1K; Resistor (0805)
R2, R6, R8, R9, R11, R15, R16, R19, R20, R21, R58, R59, R78, R79, R80, R81, R82: 1K; Resistor (0805)
R4: 1M; Resistor (0805)
R5, R7: 27R; Resistor (0805)
R10, R12, R13, R36, R37, R38, R41, R42, R43, R44, R45, R46, R48, R50, R53, R56, R57, R72, R73, R74, R75: 10K; Resistor (0805)
R14, R17, R18, R22, R23: 100R; Resistor (0805)
R24, R25, R26, R27: 22R; Resistor (0805)
R28, R29, R30, R31, R32, R33, R34, R35: 270R; Resistor (0805)
R39, R40, R54, R55, R60, R61, R68, R69, R70, R71: 2K; Resistor (0805)
R47, R52: 20K; Resistor (0805)
R49, R51: 47K; Resistor (0805)
R62, R63: 470R; Resistor (0805)
R64, R65: 120R; Resistor (0805)
R66, R67, R76, R77: 4.7K; Resistor (0805)
R83: 100K; Resistor (0805)
S1: Reset; Button (SMD, 3x3mm, 1-1)
S2: Boot; Button (SMD, 3x3mm, 1-1)
S3: KLS7-TS3302; Button (SMD, 3x3mm, 1-1)
U1: NCP1117 3.3; SOT-223
U2: W25Q128JVSIQ; SOIC-8
U3: RP2040; QFN 56
U4: ESP-PSRAM32; SO-8
U5: MW7211A; SOP-16
U6: 74HC4052D; 74HC4052D653
U7: TS3USB221RSER; UQFN-10
U8: PAM8403D; SOIC127P600X175-16N
U9: LM358; SO-8
U10: TDA1387T; SO-8
U11, U12: YM3439-F
U13, U14: 74HC595; SOP-16
U15: 74HC74; 74HCT74D
X1: 3.58 MHz; Crystal (HC49-S)
Y1: 12 MHz; Crystal (3225)

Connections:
+3V3: C2.1, C5.1, C6.1, C7.1, C8.1, C9.1, C10.1, C11.1, C12.1, C14.1, C15.1, C18.2, C19.1, C21.1, C28.2, J2.1, J4.P4 (VDD), J5.4 (VDD), R2.2, R10.1, R11.1, R38.1, U1.2 (VO), U2.8 (VCC), U3.1 (IOVDD), U3.10 (IOVDD), U3.22 (IOVDD), U3.33 (IOVDD), U3.42 (IOVDD), U3.43 (ADC_AVDD), U3.44 (VREG_IN), U3.48 (USB_VDD), U3.49 (IOVDD), U4.8 (VCC), U7.10 (VCC)
/AMP_IN_L: C36.1, R44.1, U6.13 (1Z)
/AMP_IN_R: C38.1, R45.1, U6.3 (2Z)
/Audio Out/AMP_OUTL: C37.2, J8.T, R47.2
/Audio Out/AMP_OUTR: C39.2, J8.R, R52.2
/Audio Out/AMP_PAM_OUTL_M: J6.2, U8.3 (-OUTL)
/Audio Out/AMP_PAM_OUTL_P: J6.1, U8.1 (+OUT_L)
/Audio Out/AMP_PAM_OUTR_M: J7.2, U8.14 (-OUT_R)
/Audio Out/AMP_PAM_OUTR_P: J7.1, U8.16 (+OUT_R)
/Audio Out/Amplifier/ MONO_L: C30.1, JP3.1, R39.1, R44.2
/Audio Out/Amplifier/MONO_R: C33.1, JP3.2, R40.1, R45.2
/Audio Out/TS/BEEP: R72.2, R73.2, U14.4 (QE)
/Audio Out/TS/CLK_1.75M: U11.19 (CLOCK), U12.19 (CLOCK), U15.5 (Q)
/Audio Out/TS/DA0: U11.34 (DA0), U12.34 (DA0), U13.15 (QA)
/Audio Out/TS/DA1: U11.33 (DA1), U12.33 (DA1), U13.1 (QB)
/Audio Out/TS/DA2: U11.32 (DA2), U12.32 (DA2), U13.2 (QC)
/Audio Out/TS/DA3: U11.31 (DA3), U12.31 (DA3), U13.3 (QD)
/Audio Out/TS/DA4: U11.30 (DA4), U12.30 (DA4), U13.4 (QE)
/Audio Out/TS/DA5: U11.29 (DA5), U12.29 (DA5), U13.5 (QF)
/Audio Out/TS/DA6: U11.28 (DA6), U12.28 (DA6), U13.6 (QG)
/Audio Out/TS/DA7: U11.27 (DA7), U12.27 (DA7), U13.7 (QH)
/Audio Out/TS/SAVE: R74.2, R75.2, U14.5 (QF)
/Audio Out/TS/YM_BC1: U11.26 (BC1), U12.26 (BC1), U14.15 (QA)
/Audio Out/TS/YM_BDIR: U11.24 (BDIR), U12.24 (BDIR), U14.1 (QB)
/Audio Out/TS/YM_CS1: LD3.2 (A), U11.22 (A8), U12.22 (A8), U14.2 (QC)
/Audio Out/TS/YM_CS2: LD4.2 (A), U14.3 (QD)
/Audio Out/TS/YM_RST: D7.2 (A), D8.2 (A), U11.20 (RESET), U12.20 (RESET)
/Audio Out/TS/YM_SEL1: R80.2, R81.2, U11.23 (SEL), U12.23 (SEL)
/D+: R5.1, U7.8 (D+)
/D-: R7.1, U7.7 (D-)
/DAT1: J4.P8 (DAT1), J5.8 (DAT1)
/DAT2: J4.P1 (DAT2), J5.1 (DAT2)
/GPIO0: D3.1 (K), J1.2, R17.2, U3.2 (GPIO0)
/GPIO1: D4.1 (K), J1.3, R18.2, U3.3 (GPIO1)
/GPIO2: J4.P5 (CLK), J5.5 (CLK), U3.4 (GPIO2)
/GPIO3: J4.P3 (CMD), J5.3 (CMD), U3.5 (GPIO3)
/GPIO4: J4.P7 (DAT0), J5.7 (DAT0), U3.6 (GPIO4)
/GPIO5: J4.P2 (CD/DAT3), J5.2 (DAT3/CD), U3.7 (GPIO5)
/GPIO6: R28.2, U3.8 (GPIO6)
/GPIO7: R29.2, U3.9 (GPIO7)
/GPIO8: R30.2, U3.11 (GPIO8)
/GPIO9: R31.2, U3.12 (GPIO9)
/GPIO10: R32.2, U3.13 (GPIO10)
/GPIO11: R33.2, U3.14 (GPIO11)
/GPIO12: R34.2, U3.15 (GPIO12)
/GPIO13: R35.2, U3.16 (GPIO13)
/GPIO14: J10.4, JP1.7, U3.17 (GPIO14)
/GPIO15: J10.3, JP1.6, U3.18 (GPIO15)
/GPIO16: D2.1 (K), R15.1, U3.27 (GPIO16)
/GPIO18: U3.29 (GPIO18), U4.1 (~CE)
/GPIO19: U3.30 (GPIO19), U4.6 (SCLK)
/GPIO20: U3.31 (GPIO20), U4.5 (SI/SIO)
/GPIO21: JP2.2 (B), U3.32 (GPIO21)
/GPIO22: Q1.3 (C), R11.2, U3.34 (GPIO22)
/GPIO26: R59.2, U3.38 (GPIO26_ADC0), U10.3 (DATA), U13.12 (RCLK), U14.12 (RCLK)
/GPIO27: R58.2, U3.39 (GPIO27_ADC1), U10.1 (SCLK), U13.11 (SRCLK), U14.11 (SRCLK)
/GPIO28: R54.1, R55.1, U3.40 (GPIO28_ADC2), U10.2 (LRCK), U13.14 (SER)
/HUB_D+: U5.11 (DPU), U7.1 (1D+)
/HUB_D-: U5.10 (DMU), U7.2 (1D-)
/J_TDA: JP1.1, R36.2, U6.10 (S0)
/J_TS: JP1.2, R37.2, U6.9 (S1)
/KB_CLK: J11.5, R16.2, R17.1
/KB_DATA: J11.1, R18.1, R19.2
/MS_CLK: J11.6, R21.2, R23.1
/MS_CLK_3V: D6.1 (K), JP1.4, R23.2
/MS_DATA: J11.2, R20.2, R22.1
/MS_DATA_3V: D5.1 (K), JP1.5, R22.2
/PWM_OUT_L: R57.2, R61.1, U6.12 (1Y0)
/PWM_OUT_R: R56.2, R60.1, U6.1 (2Y0)
/RP2040/GPIO25: R9.2, U3.37 (GPIO25)
/RP2040/QSPI_SCLK: U2.6 (CLK), U3.52 (QSPI_SCLK)
/RP2040/QSPI_SD0: U2.5 (DI(IO0)), U3.53 (QSPI_SD0)
/RP2040/QSPI_SD1: U2.2 (DO(IO1)), U3.55 (QSPI_SD1)
/RP2040/QSPI_SD2: U2.3 (IO2), U3.54 (QSPI_SD2)
/RP2040/QSPI_SD3: U2.7 (IO3), U3.51 (QSPI_SD3)
/RP2040/QSPI_SS: R6.1, U2.1 (~CS), U3.56 (QSPI_SS)
/RP2040/XIN: C17.1, U3.20 (XIN), Y1.1
/RP2040/XOUT: R8.1, U3.21 (XOUT)
/RUN: S1.1, U3.26 (RUN)
/SHND: R42.2, U8.12 (SHND)
/TDA_L: R63.2, U6.14 (1Y1), U10.6 (A_LEFT)
/TDA_R: R62.1, U6.5 (2Y1), U10.8 (A_RIGHT)
/TS_L: R64.1, R66.1, R67.1, R70.1, R71.1, R73.1, R75.1, U6.15 (1Y2)
/TS_R: R65.1, R68.1, R69.1, R72.1, R74.1, R76.1, R77.1, U6.2 (2Y2)
/USBMPXSW: JP1.3, R38.2, U7.9 (S)
/USB_D1+: R24.1, U5.8 (DP3)
/USB_D1-: R26.1, U5.7 (DM3)
/USB_D2+: R25.1, U5.6 (DP2)
/USB_D2-: R27.1, U5.5 (DM2)
/UTC_D+: J3.6 (DP1), J3.8 (DP2), U7.3 (2D+)
/UTC_D-: J3.5 (DN2), J3.7 (DN1), U7.4 (2D-)
GND: C1.2, C2.2, C3.2, C4.2, C5.2, C6.2, C7.2, C8.2, C9.2, C10.2, C11.2, C12.2, C13.2, C14.2, C15.2, C16.2, C17.2, C18.1, C19.2, C21.2, C22.2, C23.2, C24.2, C25.2, C26.2, C27.1, C28.1, C29.2, C31.2, C32.2, C34.1, C35.1, C40.1, C41.2, C42.2, C43.2, C44.2, C45.2, C46.2, C47.2, C48.2, C49.2, C50.2, C51.1, C52.1, D2.2 (A), D3.2 (A), D4.2 (A), D5.2 (A), D6.2 (A), J1.1, J2.2, J3.1 (GND), J3.12 (GND), J4.G1 (GND_1), J4.G2 (GND_2), J4.G3 (GND_3), J4.P6 (VSS), J5.6 (VSS), J8.S, J9.S, J10.8, J11.3, J12.4 (GND1), J12.8 (GND2), J12.9 (Shield), J13.2 (G_D2), J13.5 (G_D1), J13.8 (G_D0), J13.11 (G_CLK), J13.17 (G_DDC/CEC), J13.20 (SHIELD1), J13.21 (SHIELD2), J13.22 (SHIELD3), J13.23 (SHIELD4), JP1.8, LD1.1 (K), LD2.1 (K), Q1.2 (E), Q2.2 (E), Q3.2 (E), R1.1, R3.1, R4.2, R14.2, R36.1, R37.1, R39.2, R40.2, R47.1, R52.1, R53.1, R60.2, R61.2, R62.2, R63.1, R64.2, R65.2, R78.1, R79.1, S1.2, S2.2, S3.2, U1.1 (GND), U2.4 (GND), U3.19 (TESTEN), U3.57 (GND), U4.4 (VSS), U5.15 (GND), U5.16 (GND), U6.4 (2Y3), U6.6 (~E), U6.7 (VEE), U6.8 (GND), U6.11 (1Y3), U7.5 (GND), U7.6 (~OE), U8.2 (PGND), U8.11 (GND), U8.15 (PGND), U9.4 (V-), U10.4 (AGND), U11.21 (A9), U11.40 (VSS), U12.21 (A9), U12.40 (VSS), U13.8 (GND), U13.13 (~OE), U14.8 (GND), U14.13 (~OE), Y1.2, Y1.4
unnamed: C16.1, R8.2, Y1.3
unnamed: C20.1, J9.T, R14.1
unnamed: C20.2, R13.1
unnamed: C30.2, R41.2
unnamed: C33.2, R43.2
unnamed: C36.2, R48.2
unnamed: C37.1, R49.1, U9.7
unnamed: C38.2, R50.2
unnamed: C39.1, R51.1, U9.1
unnamed: C41.1, R54.2, R56.1, R59.1
unnamed: C42.1, R55.2, R57.1, R58.1
unnamed: D1.2 (A), Q2.3 (C), R10.2, R12.1
unnamed: D1.1 (K), Q2.1 (B), R13.2
unnamed: D7.1 (K), S3.1
unnamed: D8.1 (K), U14.6 (QG)
unnamed: J3.4 (CC1), R1.2
unnamed: J3.10 (CC2), R3.2
unnamed: J3.13 (SHIELD), R4.1
unnamed: J10.2, R15.2
unnamed: J12.3 (D1+), R24.2
unnamed: J12.2 (D1-), R26.2
unnamed: J12.7 (D2+), R25.2
unnamed: J12.6 (D2-), R27.2
unnamed: J13.12 (CLKN), R28.1
unnamed: J13.10 (CLKP), R29.1
unnamed: J13.9 (D0N), R30.1
unnamed: J13.7 (D0P), R31.1
unnamed: J13.6 (D1N), R32.1
unnamed: J13.4 (D1P), R33.1
unnamed: J13.3 (D2N), R34.1
unnamed: J13.1 (D2P), R35.1
unnamed: JP2.1 (A), U4.2 (SO/SIO)
unnamed: LD1.2 (A), R2.1
unnamed: LD2.2 (A), R9.1
unnamed: LD3.1 (K), R78.2
unnamed: LD4.1 (K), R79.2
unnamed: Q1.1 (B), R12.2
unnamed: C52.2, Q3.1 (B), R83.1, X1.1
unnamed: C51.2, Q3.3 (C), R82.1, R83.2, U15.3 (C), X1.2
unnamed: R6.2, S2.1
unnamed: R7.2, U3.46 (USB_DM)
unnamed: R5.2, U3.47 (USB_DP)
unnamed: C3.1, C4.1, C13.1, U3.23 (DVDD), U3.45 (VREG_VOUT), U3.50 (DVDD)
unnamed: U5.12 (VD33), U5.14 (VD3)
unnamed: R41.1, U8.7 (INL)
unnamed: R43.1, U8.10 (INR)
unnamed: C32.1, U8.8 (VREF)
unnamed: C40.2, R46.1, R53.2, U9.3 (+), U9.5 (+)
unnamed: R50.1, R51.2, U9.2 (-)
unnamed: R48.1, R49.2, U9.6 (-)
unnamed: C43.1, U10.7 (FLT)
unnamed: R66.2, R68.2, U11.43 (CHA)
unnamed: R70.2, U11.42 (CHB)
unnamed: R76.2, U11.36 (CHC)
unnamed: R67.2, R69.2, U12.43 (CHA)
unnamed: R71.2, U12.42 (CHB)
unnamed: R77.2, U12.36 (CHC)
unnamed: U13.9 (QH'), U14.14 (SER)
unnamed: U15.2 (D), U15.6 (~Q)
VBUS: C1.1, C22.1, C23.1, C24.1, C25.1, C26.1, C27.2, C29.1, C31.1, C34.2, C35.2, C44.1, C45.1, C46.1, C47.1, C48.1, C49.1, C50.1, J2.3, J3.2 (VBUS), J3.11 (VBUS), J10.6, J11.4, J12.1 (VBUS1), J12.5 (VBUS2), J13.18 (+5V), JP1.9, JP1.10, R16.1, R19.1, R20.1, R21.1, R42.1, R46.2, R80.1, R81.1, R82.2, U1.3 (VI), U5.13 (VDD5), U6.16 (VCC), U8.4 (PVDD), U8.5 (MUTE), U8.6 (VDD), U8.13 (PVDD), U9.8 (V+), U10.5 (VA), U11.25 (BC2), U11.39 (VDD), U12.25 (BC2), U12.39 (VDD), U13.10 (~SRCLR), U13.16 (VCC), U14.10 (~SRCLR), U14.16 (VCC), U15.1 (~R), U15.4 (~S)
